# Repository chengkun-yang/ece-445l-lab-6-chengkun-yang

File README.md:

## 0 Repository Structure

The typical explanation for the repo structure. Lab specific instructions can be
found further below.

### 0.1 HW

The `hw` folder should contain your schematic and board files for your PCB or
circuits. In labs 1-5 and 10, you will be creating schematics for your circuit
in KiCad.

### 0.2 SW

The `sw` folder should contain your application firmware and software written
for the lab. The `sw/inc` folder contains firmware drivers written for you by
Professor Valvano. Feel free to write your own (in fact, in some labs, you may
be required to write your own).

You can place any other source files in the `sw` folder. TAs will look at the
files you create and/or modify for software quality and for running your
project.

### 0.3 Resources

A couple files are provided in the Resources folder so you don't have to keep
searching for that one TI document. Some of them are immediately useful, like
the TM4C datasheet. Others may be useful for your final project, like the
TM4C_System_Design_Guidelines page.

### 0.4 Git and Github

We will extensively use Git and Github for managing lab projects. This makes it
easier for TAs to grade and help debug the project by allowing us to see commit
histories, maintain a common project structure, and likewise, it makes it easier
for students to collaborate with partners, merge different codebases, and to
debug their work by having a history of commits.

Two common ways of using Git and Github are [Github Desktop](https://desktop.github.com/) and the [command line](https://git-scm.com/downloads).
[Tutorials](https://dev.to/mollynem/git-github--workflow-fundamentals-5496) are also abundant on the net for you to peruse. We've provided a cheatsheet for git
in the Resources folder.

It is highly recommended to make the most out of Git, even if you've never used
it before. Version control will save you a lot of suffering, and tools like Git
or SVN are ubiquitous in the industry.

A gitignore file is added to the root of this repo that may prevent specific
files from being tagged to the repo. This are typically autogenerated output
files we don't care about, but sometimes other stuff (like .lib files) falls
through that we want. Feel free to modify if necessary.

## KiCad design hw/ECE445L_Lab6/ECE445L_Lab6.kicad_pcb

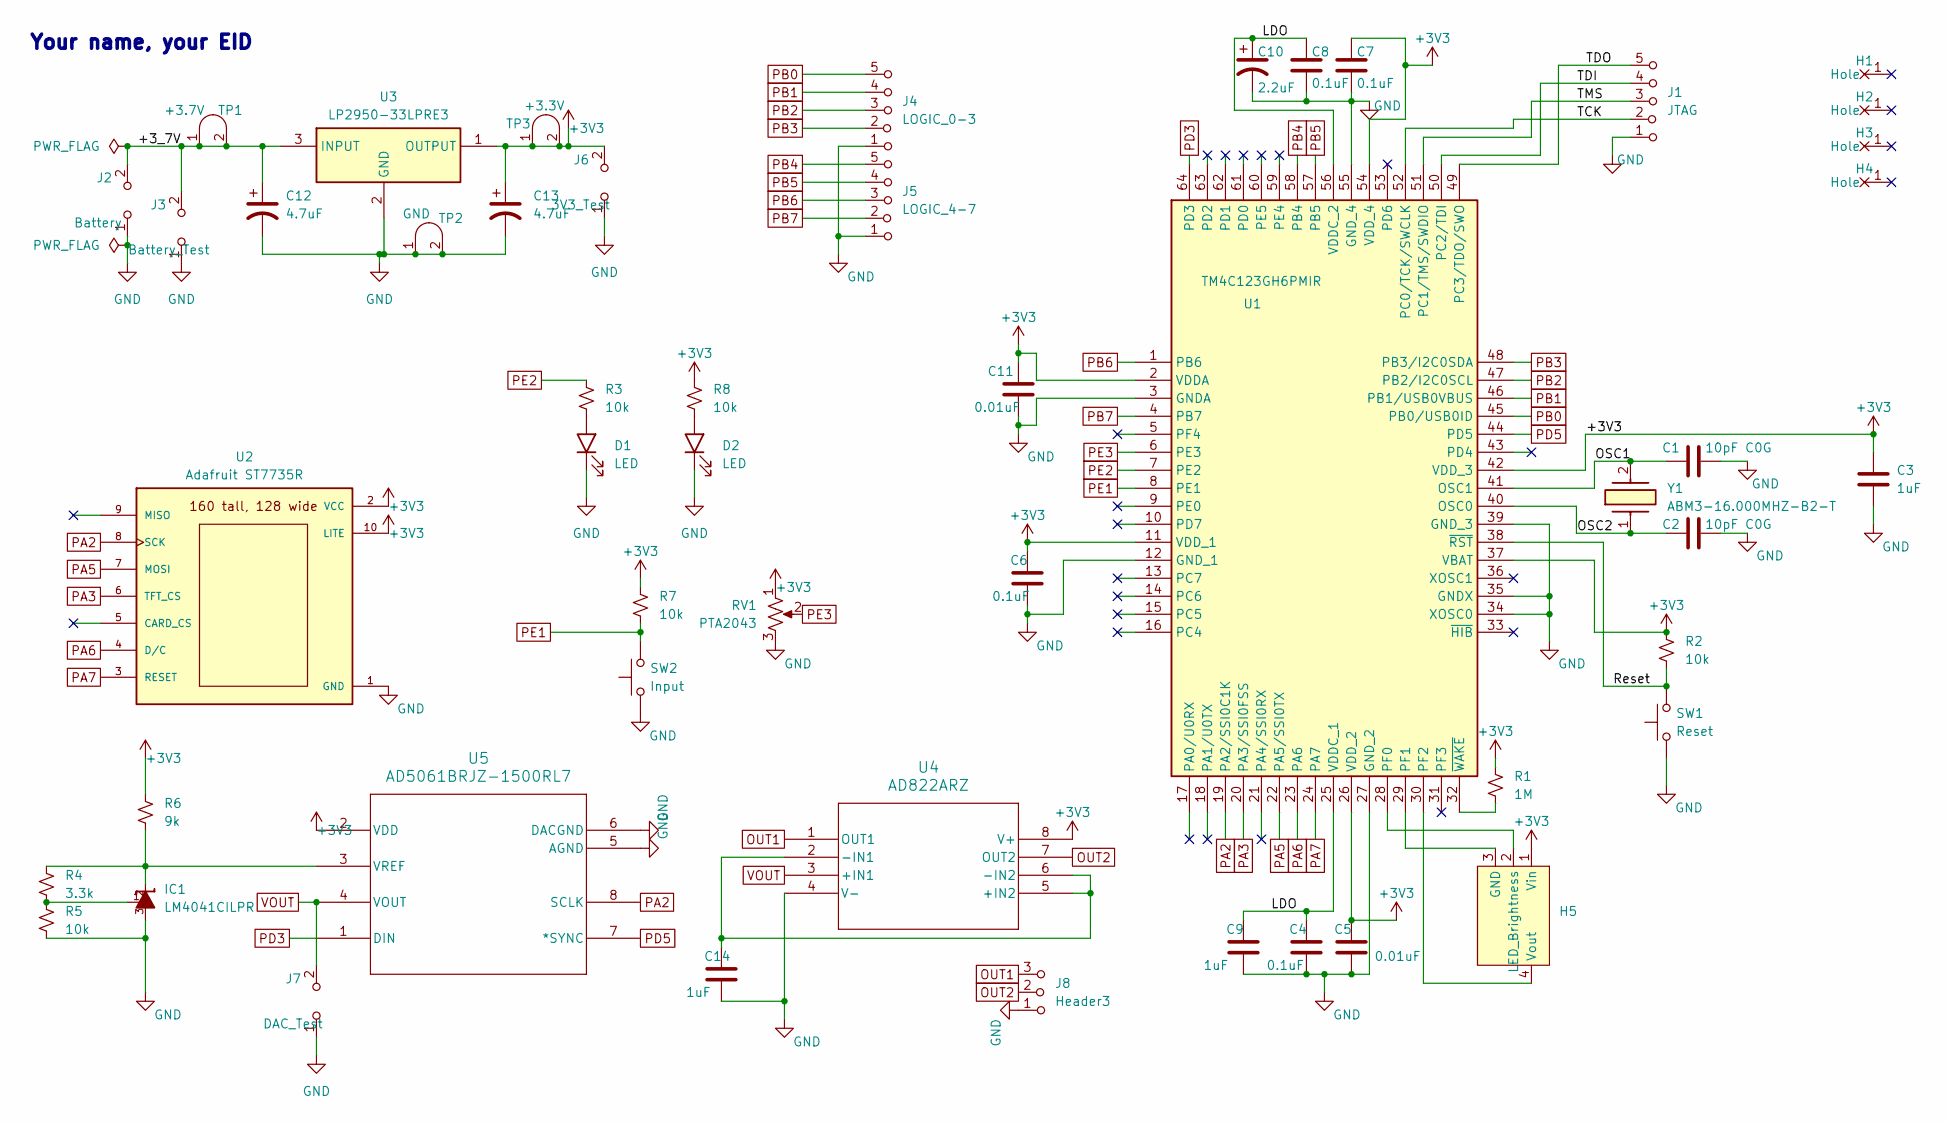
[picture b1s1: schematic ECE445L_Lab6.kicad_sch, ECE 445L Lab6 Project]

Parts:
C1, C2: 10pF C0G; C_Axial_200mil
C3, C9, C14: 1uF; C_Axial_200mil
C4, C6, C7, C8: 0.1uF; C_Axial_200mil
C5, C11: 0.01uF; C_Axial_200mil
C10: 2.2uF; CP_Radial_Tantal200mil
C12, C13: 4.7uF; CP_Radial_Tantal200mil
D1, D2: LED; LED_D5.0mm
H1, H2, H3, H4: MountingHole_4_40
H5: HEARTBEAT
IC1: LM4041CILPR; ti_LM4041CILPR
J1: JTAG; PinHeader_1x05_P2.54mm_Vertical
J2: Battery; PinHeader_1x02_P2.54mm_Vertical
J3: Battery_Test; PinHeader_1x02_P2.54mm_Vertical
J4: LOGIC_0-3; PinHeader_1x05_P2.54mm_Vertical
J5: LOGIC_4-7; PinHeader_1x05_P2.54mm_Vertical
J6: 3V3_Test; PinHeader_1x02_P2.54mm_Vertical
J7: DAC_Test; PinHeader_1x02_P2.54mm_Vertical
J8: Header3; PinHeader_1x03_P2.54mm_Vertical
R1: 1M; R_Axial_DIN0204_L3.6mm_D1.6mm_P7.62mm_Horizontal
R2, R3, R5, R7, R8: 10k; R_Axial_DIN0204_L3.6mm_D1.6mm_P7.62mm_Horizontal
R4: 3.3k; R_Axial_DIN0204_L3.6mm_D1.6mm_P7.62mm_Horizontal
R6: 9k; R_Axial_DIN0204_L3.6mm_D1.6mm_P7.62mm_Horizontal
RV1: PTA2043; PTA2043pot
SW1: Reset; SW_PUSH_6mm
SW2: Input; SW_PUSH_6mm
TP1: +3.7V; Testpoint_1x02_P2.54mm
TP2: GND; Testpoint_1x02_P2.54mm
TP3: +3.3V; Testpoint_1x02_P2.54mm
U1: TM4C123GH6PMIR; QFP50P1200X1200X160-64N; Mouser Part Number 595-TM4C123GH6PMIR
U2: Adafruit ST7735R; adafruit_st7735r2
U3: LP2950-33LPRE3; TL431CLPM; Mouser Part Number 595-LP2950-33LPRE3
U4: AD822ARZ; R_8_ADI
U5: AD5061BRJZ-1500RL7; RJ_8_ADI
Y1: ABM3-16.000MHZ-B2-T; ABM3; Mouser Part Number 815-ABM3-16-B2-T

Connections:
+3V3: C3.1, C5.1, C6.1, C7.1, C11.1, C13.1, H5.1 (Vin), J6.2 (B), R1.1, R2.1, R6.1, R7.1, R8.1, RV1.1, TP3.1 (A), TP3.2 (B), U1.2 (VDDA), U1.11 (VDD_1), U1.26 (VDD_2), U1.37 (VBAT), U1.42 (VDD_3), U1.54 (VDD_4), U2.2 (VCC), U2.10 (LITE), U3.1 (OUTPUT), U4.8 (V+), U5.2 (VDD)
/+3_7V: C12.1, J2.2 (B), J3.2 (B), TP1.1 (A), TP1.2 (B), U3.3 (INPUT)
/LDO: C4.1, C8.1, C9.1, C10.1, U1.25 (VDDC_1), U1.56 (VDDC_2)
/OSC1: C1.1, U1.41 (OSC1), Y1.2
/OSC2: C2.1, U1.40 (OSC0), Y1.1
/Reset: R2.2, SW1.2, U1.38 (~RST)
/TCK: J1.2 (B), U1.52 (PC0/TCK/SWCLK)
/TDI: J1.4 (C), U1.50 (PC2/TDI)
/TDO: J1.5 (C), U1.49 (PC3/TDO/SWO)
/TMS: J1.3 (C), U1.51 (PC1/TMS/SWDIO)
GND: C1.2, C2.2, C3.2, C4.2, C5.2, C6.2, C7.2, C8.2, C9.2, C10.2, C11.2, C12.2, C13.2, C14.2, D1.1 (K), D2.1 (K), IC1.3, J1.1 (A), J2.1 (A), J3.1 (A), J4.1 (A), J5.1 (A), J6.1 (A), J7.1 (A), J8.1 (A), R5.2, RV1.3, SW1.1, SW2.1, TP2.1 (A), TP2.2 (B), U1.3 (GNDA), U1.12 (GND_1), U1.27 (GND_2), U1.34 (XOSC0), U1.35 (GNDX), U1.39 (GND_3), U1.55 (GND_4), U2.1 (GND), U3.2 (GND), U4.4 (V-), U5.5 (AGND), U5.6 (DACGND)
unnamed: D1.2 (A), R3.2
unnamed: D2.2 (A), R8.2
unnamed: H5.3 (GND), U1.29 (PF1)
unnamed: H5.2 (LED_Brightness), U1.28 (PF0)
unnamed: H5.4 (Vout), U1.30 (PF2)
unnamed: IC1.1, R4.2, R5.1
unnamed: R1.2, U1.32 (~WAKE)
unnamed: C14.1, U4.2 (-IN1), U4.5 (+IN2), U4.6 (-IN2)
unnamed: IC1.2, R4.1, R6.2, U5.3 (VREF)
OUT1: J8.3 (C), U4.1 (OUT1)
OUT2: J8.2 (B), U4.7 (OUT2)
PA2: U1.19 (PA2/SSI0C1K), U2.8 (SCK), U5.8 (SCLK)
PA3: U1.20 (PA3/SSI0FSS), U2.6 (TFT_CS)
PA5: U1.22 (PA5/SSI0TX), U2.7 (MOSI)
PA6: U1.23 (PA6), U2.4 (D/C)
PA7: U1.24 (PA7), U2.3 (RESET)
PB0: J4.5 (C), U1.45 (PB0/USB0ID)
PB1: J4.4 (C), U1.46 (PB1/USB0VBUS)
PB2: J4.3 (C), U1.47 (PB2/I2C0SCL)
PB3: J4.2 (B), U1.48 (PB3/I2C0SDA)
PB4: J5.5 (C), U1.58 (PB4)
PB5: J5.4 (C), U1.57 (PB5)
PB6: J5.3 (C), U1.1 (PB6)
PB7: J5.2 (B), U1.4 (PB7)
PD3: U1.64 (PD3), U5.1 (DIN)
PD5: U1.44 (PD5), U5.7 (*SYNC)
PE1: R7.2, SW2.2, U1.8 (PE1)
PE2: R3.1, U1.7 (PE2)
PE3: RV1.2, U1.6 (PE3)
VOUT: J7.2 (B), U4.3 (+IN1), U5.4 (VOUT)

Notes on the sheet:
Your name, your EID

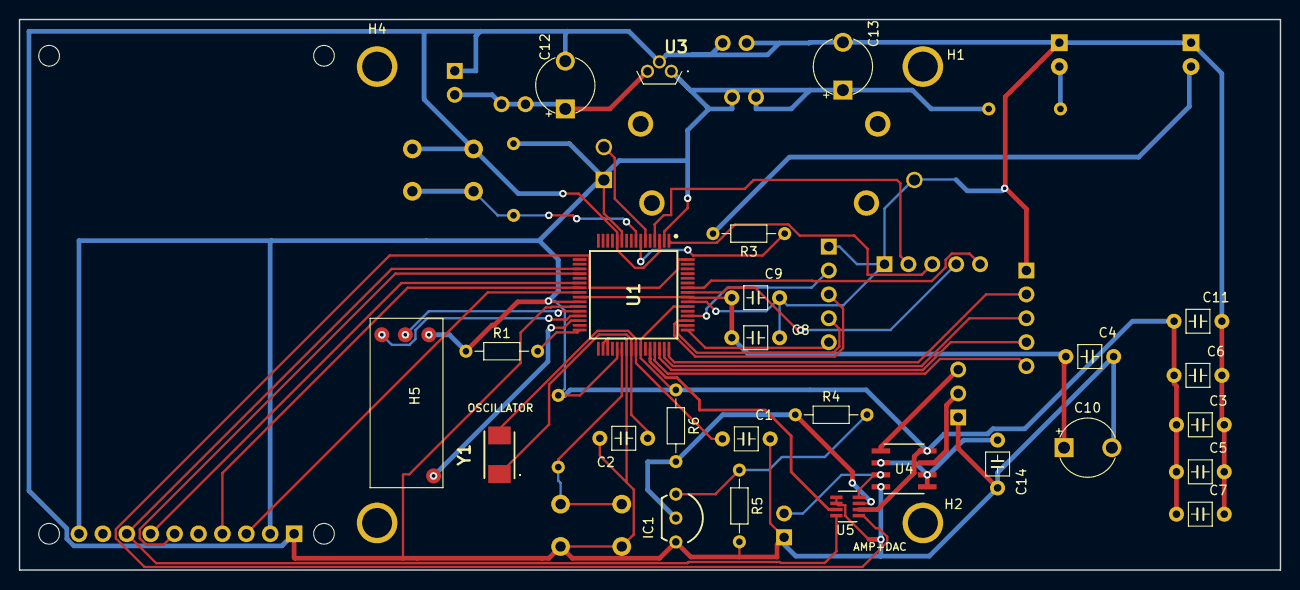
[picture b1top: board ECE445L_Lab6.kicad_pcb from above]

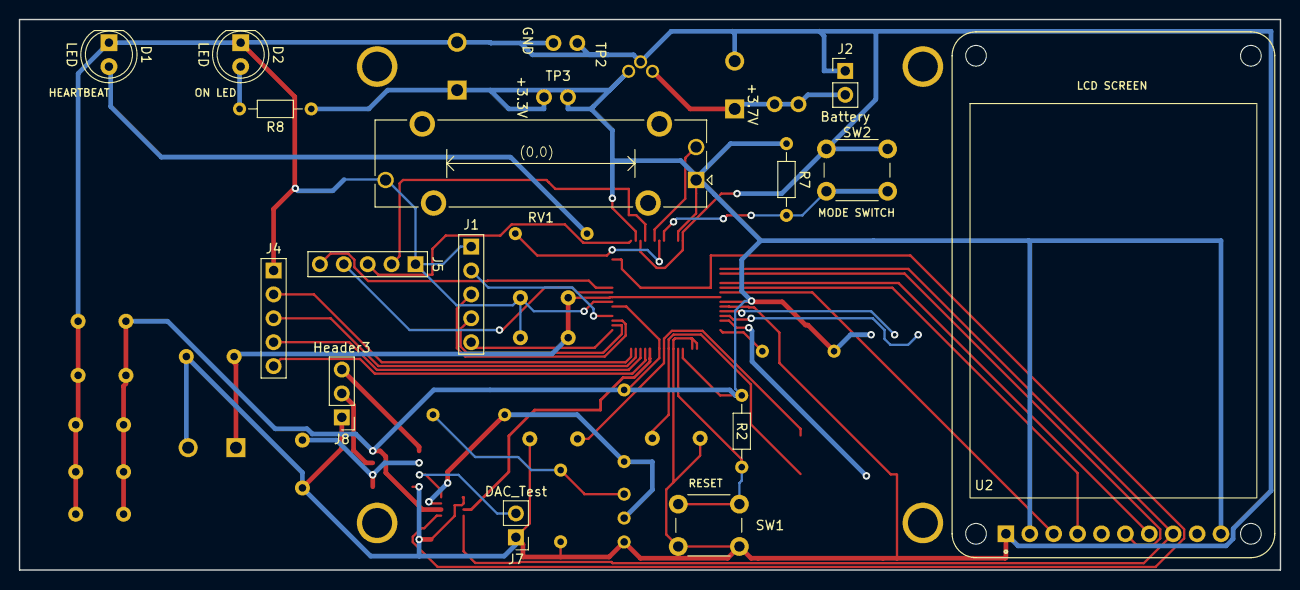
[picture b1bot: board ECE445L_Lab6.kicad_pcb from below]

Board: 2 copper layers, 134.0 x 58.5 mm, 48 parts (18 on the bottom side), 41 nets.

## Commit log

2025-02-24 flatten pt1
2025-02-24 flatten pt2
2025-02-24 flatten pt3
2025-03-02 add deadline
2025-03-07 all hardware changes
    fully updated schematic and pcb, most of changes were local to prevent corrupting files when pulling.
